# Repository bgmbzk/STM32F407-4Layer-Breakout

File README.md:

# STM32F407VGTx Yüksek Performanslı 4 Katmanlı PCB Geliştirme Kartı

Bu depo, **STM32F407VGT6** ARM Cortex-M4 mikrodenetleyicisi etrafında tasarlanmış, 4 katmanlı özgün bir basılı devre kartının (PCB) tasarım dosyalarını içermektedir.

Bu projenin temel amacı; gerçek zamanlı kontrol sistemleri, robotik uygulamalar ve yüksek kararlılık gerektiren gömülü sistem prototipleri için endüstriyel standartlarda, gürültüye dayanıklı ve güvenilir bir donanım platformu oluşturmaktır.

---

## Görseller

### 1. 3D Model Görünümü (3D Viewer)

### 2. PCB Tasarımı ve Katman Düzeni (PCB Layout)

### 3. Şematik Tasarım (Schematic Capture)

---

## Donanım Mimarısı ve Öne Çıkan Özellikler

* **Mikrodenetleyici:** STM32F407VGT6 (168 MHz ARM Cortex-M4, Donanımsal FPU, 1 MB Flash, 192 KB RAM).
* **Güç Katı ve Regülasyon:** USB Type-C (+5V) girişi, LDO regülatörüne (AMS1117-3.3) girmeden önce C12 filtresinden geçirilerek filtrelenmiş ve kararlı bir +3.3V hat oluşturulmuştur.
* **Saat/Kristal Devresi:** Hassas sistem zamanlaması için empedans uyumlu ve kısa yollarla tasarlanmış Harici Yüksek Hızlı (HSE) kristal osilatör devresi.
* **Programlama ve Debug Arayüzü:** ST-Link ile kart üzerinde canlı hata ayıklama (Hardware In-Circuit Debugging) imkanı sunan 4 pinli SWD (Serial Wire Debug) konnektörü.
* **Bağlantı ve Koruma:** Şasi/GND koruma via'ları ile izole edilmiş ve paraziti önlenmiş USB 2.0 veri arayüzü.

---

## 4 Katmanlı PCB Stackup ve Güç İzolasyonu (Power Integrity)

Sinyal bütünlüğünü artırmak, elektromanyetik paraziti (EMI) en aza indirmek ve kararlı bir güç dağıtımı sağlamak amacıyla geleneksel 2 katmanlı tasarım yerine **4 katmanlı katman yapısı (stackup)** tercih edilmiştir:

1. **Üst Katman (`F.Cu`):** Yüksek hızlı sinyal hatları (Kristal, USB Veri hatları, SWD) ve bileşen bağlantıları.
2. **İç Katman 1 (`In1.Cu`):** Kesintisiz, düşük empedanslı dönüş yolları sağlayan özel **Toprak Düzlemi (GND Plane)**.
3. **İç Katman 2 (`In2.Cu`):** Düşük endüktanslı güç dağıtımı sağlayan özel **Güç Düzlemi (+3.3V Plane)**.
4. **Alt Katman (`B.Cu`):** İkincil sinyal hatları ve ek termal rahatlama alanı.

---

## Dosya Yapısı

```text
├── Hardware/
│   ├── STM32_Breakout.kicad_pcb    # KiCad PCB Çizim Dosyası
│   ├── STM32_Breakout.kicad_sch    # Şematik Çizim Dosyası
│   └── KiCad Proje Dosyaları
├── Fabrication/
│   ├── Gerbers/                     # Üretime Hazır Gerber Dosyaları
│   └── Drill/                       # Drill (Delik) Dosyaları
├── images/
│   ├── schematic.png                # Şematik Ekran Görüntüsü
│   ├── pcb_layout.png               # PCB Çizim Ekran Görüntüsü
│   └── pcb_3d.png                   # 3D Model Ekran Görüntüsü
└── README.md

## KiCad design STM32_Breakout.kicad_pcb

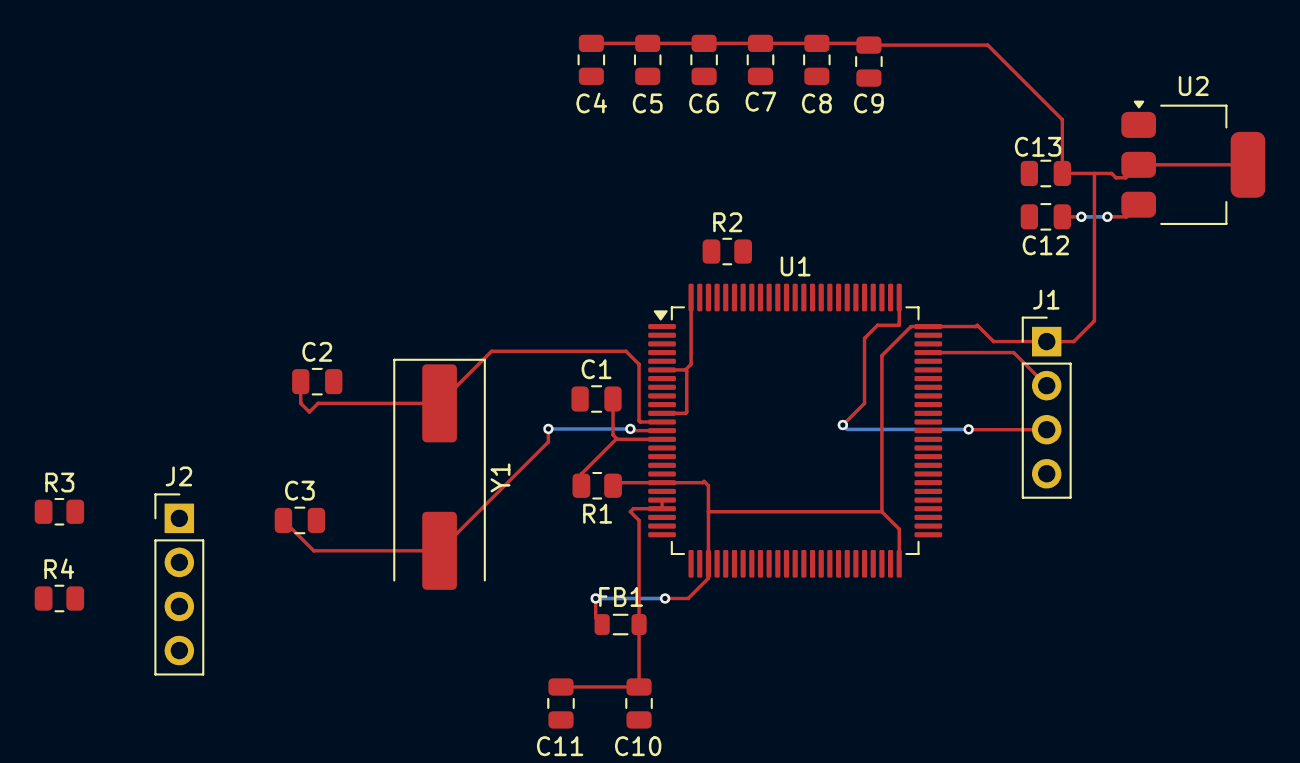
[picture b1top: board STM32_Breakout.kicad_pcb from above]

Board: 2 copper layers, 23 parts (0 on the bottom side), 10 nets.

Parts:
C1, C10: 100nF; C_0805_2012Metric
C2, C3: 22pF; C_0805_2012Metric
C4, C5, C6, C7, C8, C9: 0.1uF; C_0805_2012Metric
C11: 1μF; C_0805_2012Metric
C12, C13: 10μF; C_0805_2012Metric
FB1: FerriteBead_Small; L_0805_2012Metric
J1: Conn_01x04_Pin; PinHeader_1x04_P2.54mm_Vertical
J2: USB_C_Receptacle_USB2.0_16P; PinHeader_1x04_P2.54mm_Vertical
R1, R2: 10k; R_0805_2012Metric
R3, R4: 5.1kΩ; R_0805_2012Metric
U1: STM32F407VGTx; LQFP-100_14x14mm_P0.5mm
U2: AMS1117-3.3; SOT-223-3_TabPin2
Y1: Crystal; Crystal_SMD_HC49-SD

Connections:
+3.3V: C4.1, C5.2, C6.2, C7.2, C8.2, C9.2, C13.2, FB1.1, J1.1, R1.1, U1.6 (VBAT), U1.11 (VDD), U1.19 (VDD), U1.28 (VDD), U1.50 (VDD), U1.75 (VDD), U1.100 (VDD), U2.2 (VO)
+5V: C12.1, U2.3 (VI)
/SWCLK: J1.3, U1.76 (PA14)
/SWDIO: J1.2, U1.72 (PA13)
GND: C1.1, C2.2, C3.2, C4.2, C5.1, C6.1, C7.1, C8.1, C9.1, C10.1, C11.2, C12.2, C13.1, J1.4, R2.1, R3.2, R4.2, U2.1 (GND)
unnamed: R2.2, U1.94 (BOOT0)
unnamed: C1.2, R1.2, U1.14 (NRST)
unnamed: C2.1, U1.12 (PH0), Y1.1
unnamed: C3.1, U1.13 (PH1), Y1.2
unnamed: C10.2, C11.1, FB1.2, U1.21 (VREF+), U1.22 (VDDA)
